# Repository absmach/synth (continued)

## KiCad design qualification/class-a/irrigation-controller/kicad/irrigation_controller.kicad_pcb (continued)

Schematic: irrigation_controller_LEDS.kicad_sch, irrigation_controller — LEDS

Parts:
D_N1: (no value); LED_0603_1608Metric
D_PWR: LTST-C190KGKT; LED_0603_1608Metric; MPN LTST-C190KGKT
D_VALVE: (no value); LED_0603_1608Metric
R_LV: 680; R_0603_1608Metric
R_N3: 2.2k; R_0603_1608Metric
R_PWR: 680; R_0603_1608Metric

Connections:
+3V3: R_PWR.1; also elsewhere on the board
+12V_VALVE: R_N3.1; also elsewhere on the board
GND: D_N1.1 (K), D_PWR.1 (K), D_VALVE.1 (K); also elsewhere on the board
LED_N12_A: D_N1.2 (A), R_N3.2
LED_PWR_A: D_PWR.2 (A), R_PWR.2
LED_VALVE_A: D_VALVE.2 (A), R_LV.2
LED_VALVE_DRV: R_LV.1; also elsewhere on the board

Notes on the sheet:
LEDS
D_PWR lit when +3V3 is present. D_VALVE lit when firmware commands either valve on.
D_N1 lit when +12V_VALVE is present (R_N3).
LED currents are I = (V - Vf) / R, with Vf from the LED datasheets: Lite-On LTST-C190KGKT 1.9 to 2.4 V at 20 mA (green LED D_PWR), KENTO KT-0603Y 2.4 V (amber LEDs D_VALVE and D_N1, from its LCSC listing). D_PWR, R_PWR 680 on +3V3: 1.3 to 2.1 mA, at most 4.85 mA with Vf = 0. D_VALVE, R_LV 680, driv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

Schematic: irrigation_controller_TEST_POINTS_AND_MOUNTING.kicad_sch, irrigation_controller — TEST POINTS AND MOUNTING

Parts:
H1, H2, H3, H4: (no value); MountingHole_2.5mm
TP_N1, TP_N2: (no value); TestPoint_Pad_D1.5mm

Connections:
+3V3: TP_N1.1; also elsewhere on the board
GND: TP_N2.1; also elsewhere on the board

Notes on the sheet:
TEST POINTS AND MOUNTING
TP_N1 on +3V3, TP_N2 on GND.
Four M2.5 mounting holes at the corners.

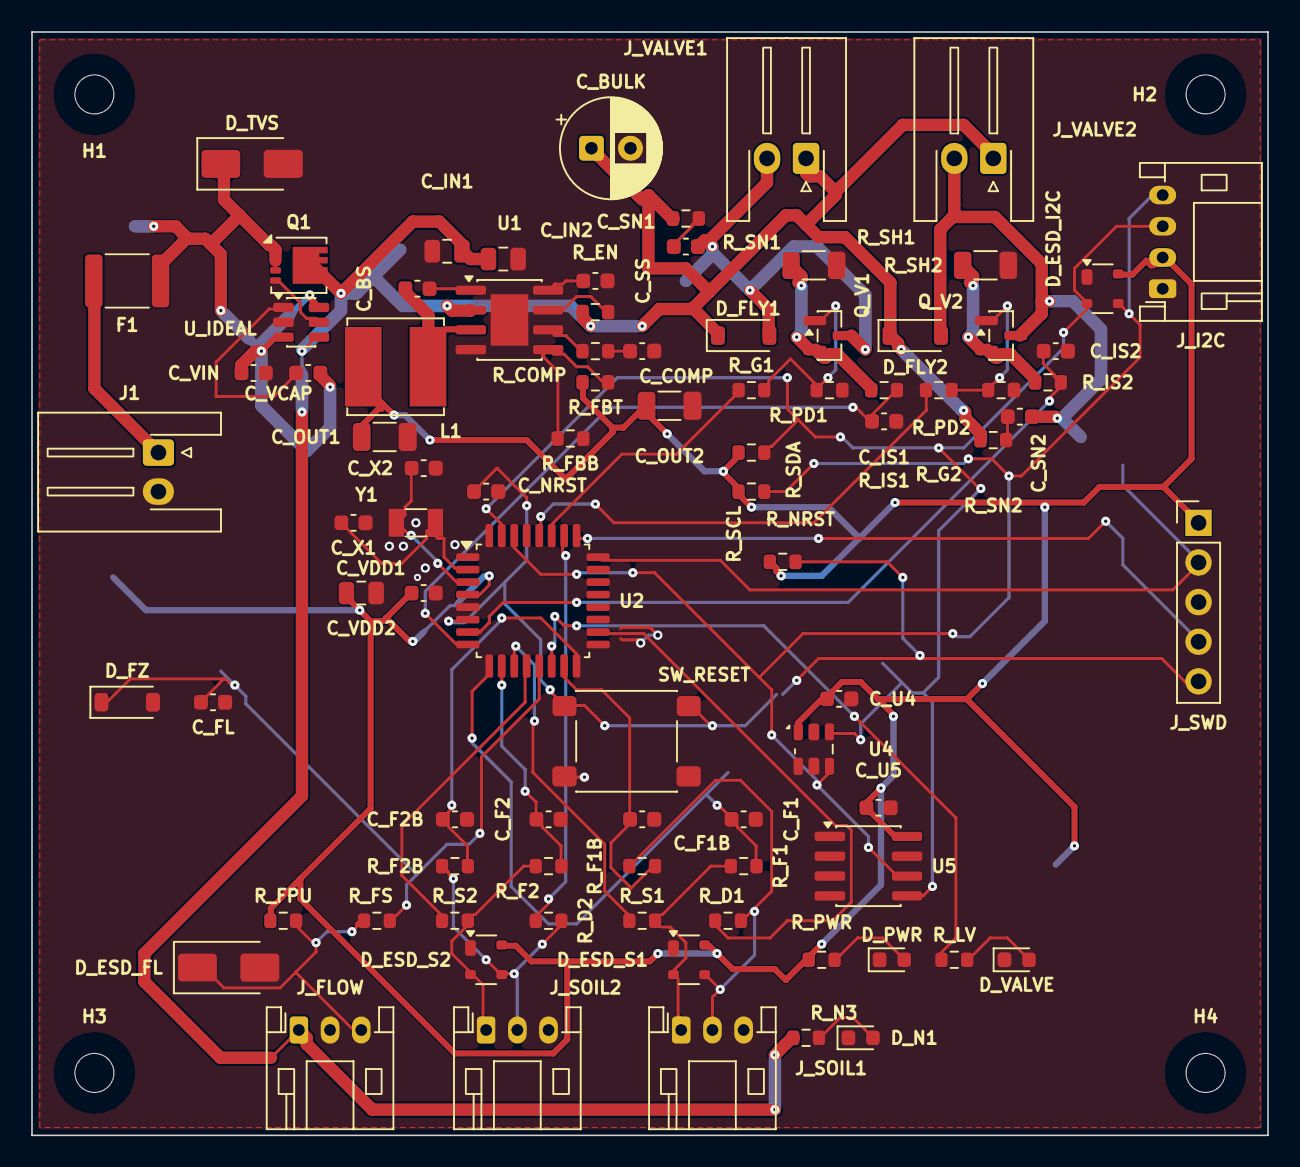
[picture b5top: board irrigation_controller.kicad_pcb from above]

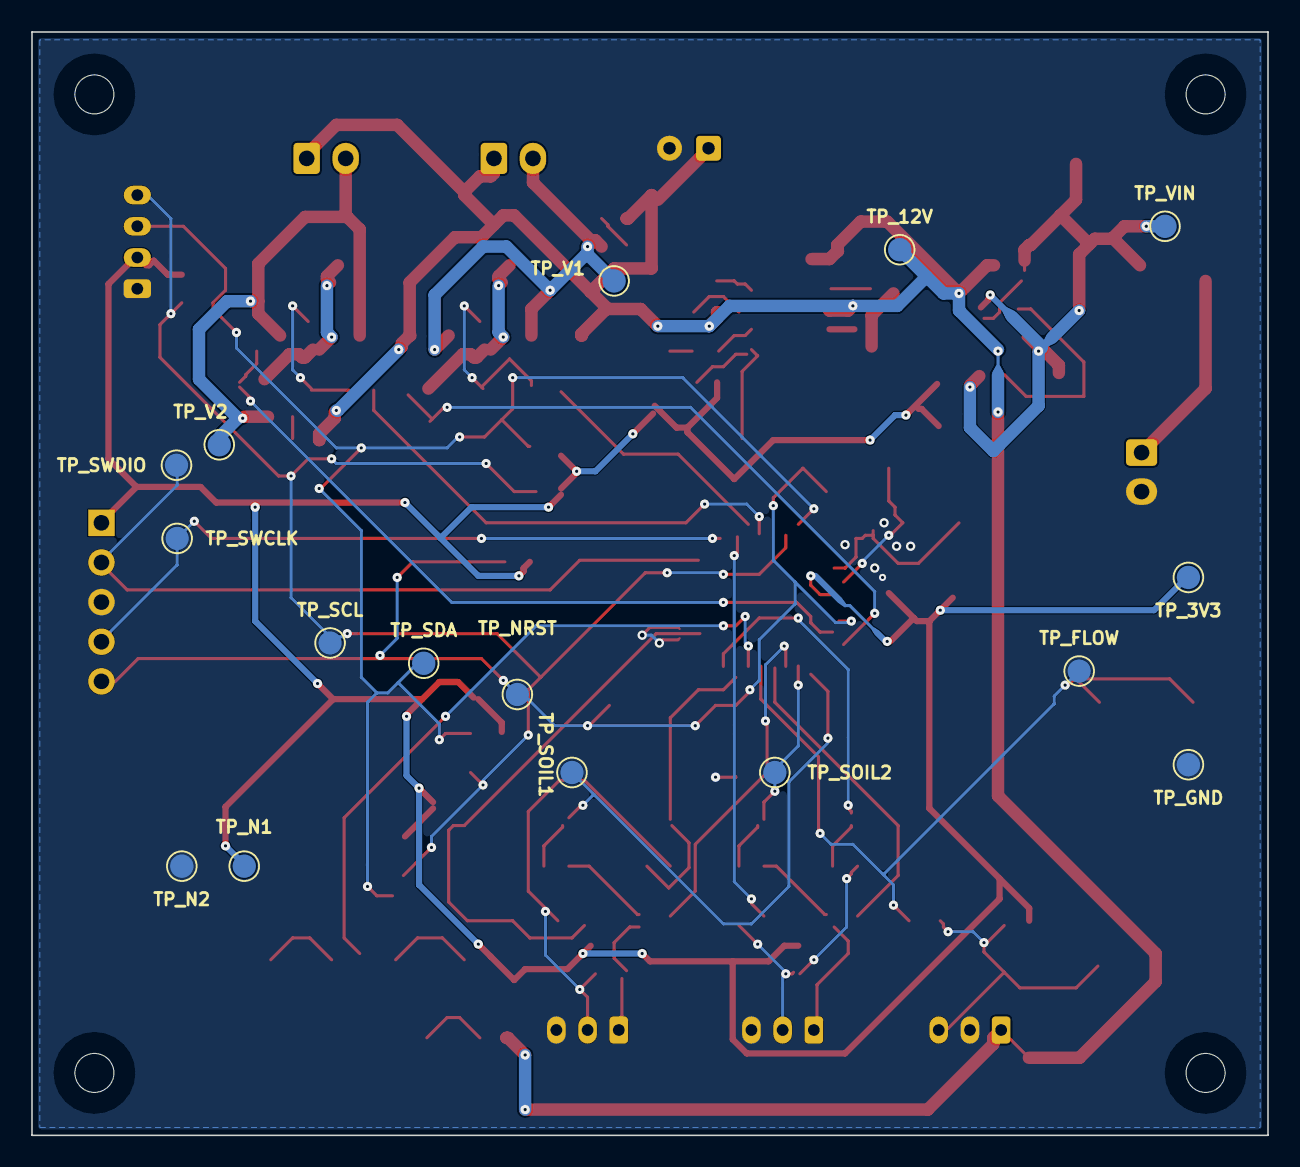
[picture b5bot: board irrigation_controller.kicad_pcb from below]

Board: 2 copper layers, 79.2 x 70.7 mm, 107 parts (16 on the bottom side), 51 nets.

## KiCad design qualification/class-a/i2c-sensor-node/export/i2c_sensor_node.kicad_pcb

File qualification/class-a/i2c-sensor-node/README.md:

# I2C sensor node with a 5 V JST input (Class A, case 2)

A field sensor node: an STM32G030F6P6 microcontroller reads a Bosch BME680 (temperature, humidity, pressure and gas) and a 24LC256 EEPROM over one I2C bus. It runs from 5 V on a JST XH connector, with an AMS1117-3.3 making the 3.3 V rail. The board has two copper layers with a GND pour on each and measures 84.0 x 50.0 mm.

Case 2 is claimed for a plain default export of a protected, low-speed board: every external line has a series resistor and a 3.3 V clamp, and every net is a static or slow line. No firmware has run on the board and no board has been built.

The prompt to reproduce the board is in [`PROMPT.md`](PROMPT.md), written from the finished board. The prompts the agent ran are in the history at `dcf1e328`.

## The board

### Parts

| Group            | Parts                                                                                                                                                                                                         |
| ---------------- | ------------------------------------------------------------------------------------------------------------------------------------------------------------------------------------------------------------- |
| 5 V input        | `J1` JST S2B-XH-A-1; `F1` Littelfuse 1812L050/60MR (0.5 A hold); `D1` 1N5819HW Schottky against reverse polarity; `D4` Nexperia PTVS6V0S1UR (6 V standoff, 10.3 V maximum clamp per the distributor listings) |
| 3.3 V            | `U1` AMS1117-3.3 (SOT-223); `C1`, `C2` 10 uF on the input; `C3` 47 uF tantalum, `C4` 10 uF and `C5` 100 nF on the output; power LED `D15` with `R24`                                                          |
| Microcontroller  | `U2` STM32G030F6P6 (TSSOP-20); `C6` 100 nF and `C7` 4.7 uF on VDD; `R3` 10 k, `C8` 100 nF and `SW1` on NRST; `J4` 1x5 SWD header behind `R13`, `R14` (100 ohm), with 3.3 V zeners `D8`, `D9`, `D19`           |
| I2C sensing      | `U3` BME680 and `U5` 24LC256 on one bus (PB7 SDA, PB6 SCL), pull-ups `R9`, `R10` (4.7 k), decoupling `C10` to `C12`                                                                                           |
| Serial connector | `J3` JST S4B-PH-K-S: UART TX through `R11` (330 ohm) and `D7`, RX through `R12` (1 k) and `D24`, 3.3 V sense and ground                                                                                       |
| GPIO header      | `J5` 1x12 header: eight MCU lines (ADC, SPI and timer pins), each behind 330 ohm (`R15` to `R22`) with a 3.3 V zener (`D10` to `D13`, `D20` to `D23`); a 3.3 V sense line through `D14` and `R23` (100 ohm)   |
| Mounting         | `H2`, `H3`: two M2.5 non-plated holes at opposite corners                                                                                                                                                     |

### Layout

| Item                    | Value                                                                                                                                                                                               |
| ----------------------- | --------------------------------------------------------------------------------------------------------------------------------------------------------------------------------------------------- |
| Outline                 | 84.0 x 50.0 mm                                                                                                                                                                                      |
| Copper layers           | 2 (F.Cu, B.Cu)                                                                                                                                                                                      |
| Stackup                 | 1.6 mm board thickness                                                                                                                                                                              |
| Parts in the BOM        | 57 lines: 55 parts and 2 non-plated mounting holes (`H2`, `H3`)                                                                                                                                     |
| Parts placed in the CPL | 55, all on the top side                                                                                                                                                                             |
| Nets                    | 35 named nets, counted on the board file                                                                                                                                                            |
| Track segments          | 422                                                                                                                                                                                                 |
| Vias                    | 142                                                                                                                                                                                                 |
| Track length            | 1239.4 mm                                                                                                                                                                                           |
| Zones and planes        | GND pour on F.Cu and on B.Cu; keepout zones for the `H2` and `H3` screw heads (no tracks, vias or copper pour)                                                                                      |
| Net classes             | `PWR` 0.5 mm, `V33` 0.4 mm, `GNDC` 0.4 mm and `SIG` 0.25 mm, declared in the source; `PWR`, `V33` and `SIG` declare `edge_rate slow`                                                                |
| Fab package             | `fab/gerbers.zip` (copper, mask, paste, silkscreen, outline, drill and job file), `fab/bom.csv`, `fab/cpl.csv`; KiCad project in `kicad/`, STEP model in `models/`, images in `images/`             |
| Source                  | `i2c_sensor_node.synth` with the placement sidecar `i2c_sensor_node.placement.layout.toml`; made with `synth mcp` from a prompt and exported through the Synth MCP server (the `synth_export` tool) |

### Checks

| Check                              | Result                                       | Notes                                                                     |
| ---------------------------------- | -------------------------------------------- | ------------------------------------------------------------------------- |
| KiCad DRC (10.0.8, --refill-zones) | 0 errors, 57 warnings, 0 unconnected         | Warnings: 55 lib_footprint_mismatch, 2 track_dangling                     |
| KiCad ERC (10.0.8)                 | 0 errors, 6 warnings, 0 unconnected          | Warnings: 5 lib_symbol_issues, 1 pin_to_pin                               |
| Signal class                       | No clock, differential or switching-node net | Every net is a static or slow line, as declared in the source net classes |

### Design figures

| Area             | Item                              | Value                                                                                                                             | Basis                                                                                                  |
| ---------------- | --------------------------------- | --------------------------------------------------------------------------------------------------------------------------------- | ------------------------------------------------------------------------------------------------------ |
| Power            | 3.3 V rail load budget            | 100 mA from 5 V                                                                                                                   | Stated in the source                                                                                   |
| Thermal          | `U1` dissipation at 100 mA        | (5.0 - 3.3) x 0.1 A = 0.17 W, a 15.3 C rise                                                                                       | Calculated with thetaJA 90 C/W from the AMS1117 datasheet as cited in the source; datasheet not opened |
| Thermal          | `U1` at 300 mA                    | 0.51 W, 45.9 C rise; the part's ceiling, not a supported load                                                                     | Calculated with thetaJA 90 C/W                                                                         |
| Power            | `C3` output capacitor             | 47 uF tantalum, where 22 uF is required                                                                                           | Stated in the source                                                                                   |
| Power            | Power LED current                 | 1.3 to 2.1 mA through 680 ohm at VF 1.9 to 2.4 V                                                                                  | Calculated                                                                                             |
| Protection       | Input order                       | Fuse `F1` first, then reverse-polarity diode `D1`; `D4` clamps +5V_PROT behind `D1`, so a reversed supply never forward-biases it | Stated in the source                                                                                   |
| Protection       | 5 V fault on a 330 ohm line       | (5 - 3.3) / 330 = 5.2 mA, 17 mW into its zener                                                                                    | Calculated                                                                                             |
| Protection       | 5 V fault on the 1 k UART RX line | 1.7 mA, 5.6 mW into `D24`                                                                                                         | Calculated                                                                                             |
| Protection       | 5 V fault on a 100 ohm SWD line   | (5 - 3.3) / 100 = 17 mA, 56 mW into `D8`, `D9` or `D19`                                                                           | Calculated                                                                                             |
| Protection       | 3.3 V sense line                  | At most 3 mA                                                                                                                      | Stated in the source                                                                                   |
| Signal integrity | I2C addresses                     | `U3` SDO (pin 5) tied to ground selects 0x76; `U5` A2:A0 low selects 0x50; no collision                                           | Stated in the source                                                                                   |
| Signal integrity | I2C pull-ups                      | One 4.7 k pair for the whole bus                                                                                                  | Stated in the source                                                                                   |
| Signal integrity | Unused pins                       | PA9 and PA10 (pins 16, 17) are unconnected                                                                                        | Stated in the source                                                                                   |
| Signal integrity | BOOT0                             | Shares PA14 and SWCLK; the default option bytes ignore it                                                                         | Stated in the source                                                                                   |
| Assembly         | SWD header `J4`                   | Pin 1 3.3 V sense, 2 SWDIO, 3 SWCLK, 4 GND, 5 NRST; use a J-Link or ST-LINK at 3.3 V logic                                        | Stated in the source                                                                                   |
| Assembly         | Reset                             | `SW1` and NRST on `J4` reset the chip                                                                                             | Stated in the source                                                                                   |
| Assembly         | UART connector `J3`               | Pin 1 GND, 2 UART_TX, 3 UART_RX, 4 3.3 V sense; host logic 3.3 V to 5 V                                                           | Stated in the source                                                                                   |
| Assembly         | GPIO header `J5`                  | Pin 1 3.3 V sense, 2 GND, 3 PA0, 4 PA1, 5 PA4, 6 GND, 7 PA5, 8 PA6, 9 PA7, 10 GND, 11 PB0, 12 PB9                                 | Stated in the source                                                                                   |

### Sourcing

| Item       | Status                                  | Notes                                          |
| ---------- | --------------------------------------- | ---------------------------------------------- |
| `U2`       | STM32G030F6P6TR, LCSC `C529330`         | Tape-and-reel code of the same TSSOP-20 part   |
| `SW1`      | C&K PTS645SM43SMTR92LFS, LCSC `C221880` | JLCPCB listing; re-check stock before ordering |
| `J5`       | XFCN PZ254V-11-12P, LCSC `C2840012`     | JLCPCB listing                                 |
| `J4`       | Hand-fitted, Farnell 1022253            | Harwin M20-9990546; also RS 681-2985           |
| `D4`       | Farnell (CPC) SC21458                   | No LCSC listing found                          |
| `H2`, `H3` | Board feature, no part                  | Non-plated holes                               |

## Not verified by Synth

| Area                  | What is not verified                                                                                                                            |
| --------------------- | ----------------------------------------------------------------------------------------------------------------------------------------------- |
| Routing reports       | The routing report and the return-via advisory list are not in this folder.                                                                     |
| Fabrication           | The JLCPCB DFM report and quote for this package are not in this folder.                                                                        |
| Reproducibility       | The three-export comparison and the Gerber content hash are not in this folder.                                                                 |
| Narrow copper         | The router draws 0.127 mm stubs at the pads of `U2`, below the class widths. The current they carry is not checked.                             |
| Part data             | Several BOM lines cite distributor listings only (for example `F1`, `D4`, `J5` and the `U1` thermal figures). Those datasheets were not opened. |
| Firmware and bring-up | No firmware has run and no board has been built.                                                                                                |
| Independent sign-off  | The independent PCB review required by #39 is still open.                                                                                       |

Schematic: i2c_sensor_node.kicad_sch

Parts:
C1, C2, C4: 10uF; C_0805_2012Metric
C3: 47uF; CP_EIA-3528-21_Kemet-B
C5, C6, C8, C10, C11, C12: 100nF; C_0603_1608Metric
C7: 4.7uF; C_0603_1608Metric
D1, D14: 1N5819; D_SOD-123; MPN 1N5819HW-7-F; LCSC C82544
D4: PTVS6V0S1UR; Nexperia_CFP3_SOD-123W; MPN PTVS6V0S1UR
D7, D8, D9, D10, D11, D12, D13, D19, D20, D21, D22, D23, D24: 3.3V zener; D_SOD-123
D15: GREEN; LED_0603_1608Metric; MPN LTST-C190KGKT
F1: 0.5A hold; Fuse_1812_4532Metric
H2, H3: (no value); MountingHole_2.5mm
J1: JST S2B-XH-A-1; JST_XH_S2B-XH-A-1_1x02_P2.50mm_Horizontal
J3: JST S4B-PH-K-S; JST_PH_S4B-PH-K_1x04_P2.00mm_Horizontal
J4: SWD; PinHeader_1x05_P2.54mm_Vertical
J5: GPIO; PinHeader_1x12_P2.54mm_Vertical
R3: 10k; R_0603_1608Metric
R9, R10: 4.7k; R_0603_1608Metric
R11, R15, R16, R17, R18, R19, R20, R21, R22: 330; R_0603_1608Metric
R12: 1k; R_0603_1608Metric
R13, R14: 100; R_0603_1608Metric
R23: 100; R_0805_2012Metric
R24: 680; R_0603_1608Metric
SW1: RESET; SW_SPST_PTS645Sx43SMTR92
U1: AMS1117-3.3; SOT-223-3_TabPin2; MPN AMS1117-3.3; LCSC C6186
U2: STM32G030F6P6; TSSOP-20_4.4x6.5mm_P0.65mm; MPN STM32G030F6P6
U3: BME680; Bosch_LGA-8_3x3mm_P0.8mm_ClockwisePinNumbering; MPN BME680
U5: 24LC256-I/SN; SOIC-8_3.9x4.9mm_P1.27mm; MPN 24LC256-I/SN; LCSC C411625

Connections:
3V3_REF: J3.4, J4.1, J5.1, R23.2
+3V3: C3.1, C4.1, C5.1, C6.1, C7.1, C10.1, C11.1, C12.1, D14.2 (A), R3.1, R9.1, R10.1, R24.1, U1.2 (VO), U2.4 (VDD), U3.2 (CSB), U3.6 (VDDIO), U3.8 (VDD), U5.8 (VCC)
+5V_PROT: C1.1, C2.1, D1.1 (K), D4.1 (K), U1.3 (VI)
GND: C1.2, C2.2, C3.2, C4.2, C5.2, C6.2, C7.2, C8.2, C10.2, C11.2, C12.2, D4.2 (A), D7.2 (A), D8.2 (A), D9.2 (A), D10.2 (A), D11.2 (A), D12.2 (A), D13.2 (A), D15.1 (K), D19.2 (A), D20.2 (A), D21.2 (A), D22.2 (A), D23.2 (A), D24.2 (A), J1.2, J3.1, J4.4, J5.2, J5.6, J5.10, SW1.2, U1.1 (GND), U2.5 (VSS), U3.1 (GND), U3.5 (SDO), U3.7 (GND), U5.1 (A0), U5.2 (A1), U5.3 (A2), U5.4 (GND), U5.7 (WP)
GPIO_PA0: J5.3, R15.2
GPIO_PA0_MCU: D10.1 (K), R15.1, U2.7 (PA0)
GPIO_PA1: J5.4, R16.2
GPIO_PA1_MCU: D20.1 (K), R16.1, U2.8 (PA1)
GPIO_PA4: J5.5, R17.2
GPIO_PA4_MCU: D11.1 (K), R17.1, U2.11 (PA4)
GPIO_PA5: J5.7, R18.2
GPIO_PA5_MCU: D21.1 (K), R18.1, U2.12 (PA5)
GPIO_PA6: J5.8, R19.2
GPIO_PA6_MCU: D12.1 (K), R19.1, U2.13 (PA6)
GPIO_PA7: J5.9, R20.2
GPIO_PA7_MCU: D22.1 (K), R20.1, U2.14 (PA7)
GPIO_PB0: J5.11, R21.2
GPIO_PB0_MCU: D13.1 (K), R21.1, U2.15 (PA8/PB0/PB1/PB2)
GPIO_PB9: J5.12, R22.2
GPIO_PB9_MCU: D23.1 (K), R22.1, U2.2 (PB9/PC14)
I2C_SCL: R10.2, U2.20 (PB3/PB4/PB5/PB6), U3.4 (SCK), U5.6 (SCL)
I2C_SDA: R9.2, U2.1 (PB7/PB8), U3.3 (SDI), U5.5 (SDA)
LED_PWR: D15.2 (A), R24.2
NRST: C8.1, D19.1 (K), J4.5, R3.2, SW1.1, U2.6 (NRST)
REF_D: D14.1 (K), R23.1
SWCLK: D9.1 (K), J4.3, R14.2
SWCLK_MCU: R14.1, U2.19 (PA14/PA15)
SWDIO: D8.1 (K), J4.2, R13.2
SWDIO_MCU: R13.1, U2.18 (PA13)
U2_RX: D24.1 (K), R12.1, U2.10 (PA3)
U2_TX: D7.1 (K), R11.1, U2.9 (PA2)
UART_RX: J3.3, R12.2
UART_TX: J3.2, R11.2
VIN_5V_FUSED: D1.2 (A), F1.2
VIN_5V_RAW: F1.1, J1.1

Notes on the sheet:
5V INPUT: FUSE THEN DIODE
3V3 REGULATOR
STM32G030 MCU
I2C SENSING
UART BREAKOUT
GPIO HEADER
MOUNTING
J1 pin 1 = +5 V, pin 2 = GND (JST XHP-2). Fuse first, then the
reverse-polarity diode D1.
D4 clamps transients on +5V_PROT, behind D1 so a reversed supply never
forward-biases it.
AMS1117 tab is VOUT. Load budget 100 mA: P = (5.0 - 3.3) x 0.1 A =
0.17 W, thetaJA 90 C/W gives a 15 C rise (125 C limit).
LED (VF 1.9 to 2.4 V): 1.3 to 2.1 mA through 680 R. C3 is 47 uF
tantalum (22 uF required).
J4: 1 = 3V3_REF, 2 = SWDIO, 3 = SWCLK, 4 = GND, 5 = NRST. PA14 is
SWCLK and BOOT0.
D8, D9, D19 are 3.3 V zeners; a 5 V fault through 100 R is (5 - 3.3) /
100 = 17 mA, 56 mW.
BME680 SDO low = 0x76, CSB high = I2C. 24LC256 A2:A0 low = 0x50. No
collision.
One pull-up pair, 4.7k each, for the whole bus.
J3: 1 GND, 2 UART_TX, 3 UART_RX, 4 3V3_REF (3 mA max). Host logic 3.3
V to 5 V.
D7, D24 are 3.3 V zeners behind 330 R and 1 k: a 5 V fault is 5.2 mA
(17 mW) and 1.7 mA (5.6 mW).
J5: 1 3V3_REF, 2 GND, 3 PA0, 4 PA1, 5 PA4, 6 GND, 7 PA5, 8 PA6, 9 PA7,
10 GND, 11 PB0, 12 PB9.
D10..D13, D20..D23: one 3.3 V zener per line behind 330 R; a 5 V fault
is 5.2 mA, 17 mW. 3V3_REF is +3V3 through D14 and 100 R, 3 mA max.
H2, H3: two M2.5 non-plated mounting holes at opposite (diagonal)
corners.

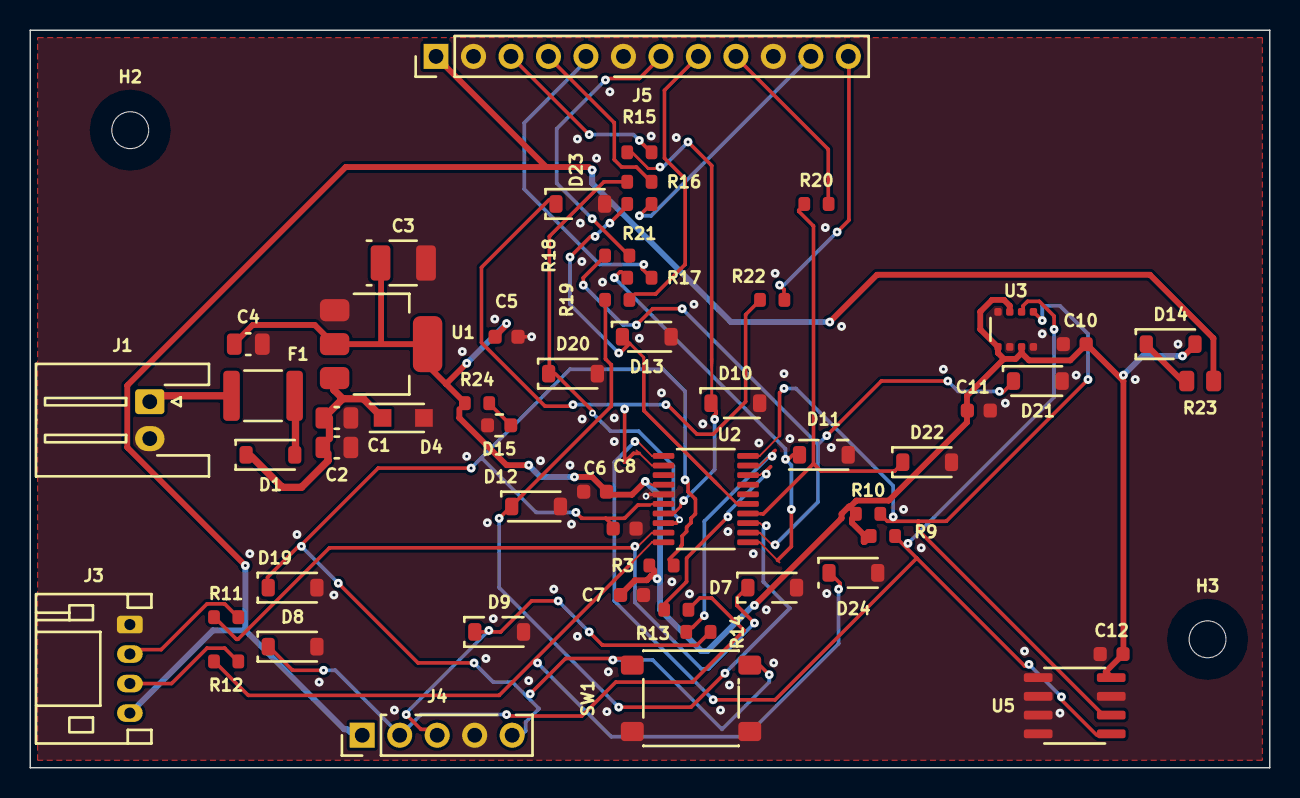
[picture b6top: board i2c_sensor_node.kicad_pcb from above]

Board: 2 copper layers, 84.0 x 50.0 mm, 57 parts (0 on the bottom side), 35 nets.

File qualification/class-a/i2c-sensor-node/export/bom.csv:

refdes,value,kind,description,kicad_symbol,kicad_footprint,lcsc_pn,mpn
C1,10uF,capacitor,"Generic 0805 MLCC, X7R/X5R, any value",Device:C,Capacitor_SMD:C_0805_2012Metric,,
C10,100nF,capacitor,"Generic 0603 MLCC, X7R/X5R, any value",Device:C,Capacitor_SMD:C_0603_1608Metric,,
C11,100nF,capacitor,"Generic 0603 MLCC, X7R/X5R, any value",Device:C,Capacitor_SMD:C_0603_1608Metric,,
C12,100nF,capacitor,"Generic 0603 MLCC, X7R/X5R, any value",Device:C,Capacitor_SMD:C_0603_1608Metric,,
C2,10uF,capacitor,"Generic 0805 MLCC, X7R/X5R, any value",Device:C,Capacitor_SMD:C_0805_2012Metric,,
C3,47uF,capacitor,"47µF 16V tantalum capacitor, polarised, 3528 case",Device:C_Polarized,Capacitor_Tantalum_SMD:CP_EIA-3528-21_Kemet-B,,
C4,10uF,capacitor,"Generic 0805 MLCC, X7R/X5R, any value",Device:C,Capacitor_SMD:C_0805_2012Metric,,
C5,100nF,capacitor,"Generic 0603 MLCC, X7R/X5R, any value",Device:C,Capacitor_SMD:C_0603_1608Metric,,
C6,100nF,capacitor,"Generic 0603 MLCC, X7R/X5R, any value",Device:C,Capacitor_SMD:C_0603_1608Metric,,
C7,4.7uF,capacitor,"Generic 0603 MLCC, X7R/X5R, any value",Device:C,Capacitor_SMD:C_0603_1608Metric,,
C8,100nF,capacitor,"Generic 0603 MLCC, X7R/X5R, any value",Device:C,Capacitor_SMD:C_0603_1608Metric,,
D1,1N5819,diode,"Diodes Inc. 1N5819HW-7-F, 40 V 1 A Schottky diode, SOD-123, low forward voltage",Device:D_Schottky,Diode_SMD:D_SOD-123,C82544,1N5819HW-7-F
D10,3.3V zener,diode,"3.3V Zener diode, SOD-123",Device:D_Zener,Diode_SMD:D_SOD-123,,
D11,3.3V zener,diode,"3.3V Zener diode, SOD-123",Device:D_Zener,Diode_SMD:D_SOD-123,,
D12,3.3V zener,diode,"3.3V Zener diode, SOD-123",Device:D_Zener,Diode_SMD:D_SOD-123,,
D13,3.3V zener,diode,"3.3V Zener diode, SOD-123",Device:D_Zener,Diode_SMD:D_SOD-123,,
D14,1N5819,diode,"Diodes Inc. 1N5819HW-7-F, 40 V 1 A Schottky diode, SOD-123, low forward voltage",Device:D_Schottky,Diode_SMD:D_SOD-123,C82544,1N5819HW-7-F
D15,GREEN,diode,"Lite-On LTST-C190KGKT green AlInGaP LED, 0603, Vf 1.9 to 2.4V at 20mA",Device:LED,LED_SMD:LED_0603_1608Metric,,LTST-C190KGKT
D19,3.3V zener,diode,"3.3V Zener diode, SOD-123",Device:D_Zener,Diode_SMD:D_SOD-123,,
D20,3.3V zener,diode,"3.3V Zener diode, SOD-123",Device:D_Zener,Diode_SMD:D_SOD-123,,
D21,3.3V zener,diode,"3.3V Zener diode, SOD-123",Device:D_Zener,Diode_SMD:D_SOD-123,,
D22,3.3V zener,diode,"3.3V Zener diode, SOD-123",Device:D_Zener,Diode_SMD:D_SOD-123,,
D23,3.3V zener,diode,"3.3V Zener diode, SOD-123",Device:D_Zener,Diode_SMD:D_SOD-123,,
D24,3.3V zener,diode,"3.3V Zener diode, SOD-123",Device:D_Zener,Diode_SMD:D_SOD-123,,
D4,PTVS6V0S1UR,diode,"Nexperia PTVS6V0S1UR 400 W unidirectional TVS, 6.0 V standoff, SOD123W, for VBUS and CC",Device:D_Zener,Diode_SMD:Nexperia_CFP3_SOD-123W,,PTVS6V0S1UR
D7,3.3V zener,diode,"3.3V Zener diode, SOD-123",Device:D_Zener,Diode_SMD:D_SOD-123,,
D8,3.3V zener,diode,"3.3V Zener diode, SOD-123",Device:D_Zener,Diode_SMD:D_SOD-123,,
D9,3.3V zener,diode,"3.3V Zener diode, SOD-123",Device:D_Zener,Diode_SMD:D_SOD-123,,
F1,0.5A hold,fuse,"Resettable polyfuse (PPTC), 0.5 A hold, 2-pin, 1812. Generic: MPN needs sourcing.",Device:Polyfuse,Fuse:Fuse_1812_4532Metric,,
H2,(no value),mounting_hole,M2.5 non-plated mounting hole (NPTH) for a board corner,Mechanical:MountingHole,MountingHole:MountingHole_2.5mm,,
H3,(no value),mounting_hole,M2.5 non-plated mounting hole (NPTH) for a board corner,Mechanical:MountingHole,MountingHole:MountingHole_2.5mm,,
J1,JST S2B-XH-A-1,connector,"JST XH-series 2-pin wire-to-board connector, 2.0mm pitch",Connector_Generic:Conn_01x02,Connector_JST:JST_XH_S2B-XH-A-1_1x02_P2.50mm_Horizontal,,
J3,JST S4B-PH-K-S,connector,"JST PH-series 4-pin wire-to-board connector, 2.0mm pitch",Connector_Generic:Conn_01x04,Connector_JST:JST_PH_S4B-PH-K_1x04_P2.00mm_Horizontal,,
J4,SWD,connector,"1x5 through-hole pin header, 2.54 mm pitch (SWD); datasheet_url is the product page of the Harwin M20 series, no manufacturer PDF link was verifiable",Connector_Generic:Conn_01x05,Connector_PinHeader_2.54mm:PinHeader_1x05_P2.54mm_Vertical,,
J5,GPIO,connector,"1x12 through-hole pin header, 2.54 mm pitch (GPIO); datasheet_url is the product page of the Harwin M20 series, no manufacturer PDF link was verifiable",Connector_Generic:Conn_01x12,Connector_PinHeader_2.54mm:PinHeader_1x12_P2.54mm_Vertical,,
R10,4.7k,resistor,"Generic 0603 thick-film resistor, any value",Device:R_US,Resistor_SMD:R_0603_1608Metric,,
R11,330,resistor,"Generic 0603 thick-film resistor, any value",Device:R_US,Resistor_SMD:R_0603_1608Metric,,
R12,1k,resistor,"Generic 0603 thick-film resistor, any value",Device:R_US,Resistor_SMD:R_0603_1608Metric,,
R13,100,resistor,"Generic 0603 thick-film resistor, any value",Device:R_US,Resistor_SMD:R_0603_1608Metric,,
R14,100,resistor,"Generic 0603 thick-film resistor, any value",Device:R_US,Resistor_SMD:R_0603_1608Metric,,
R15,330,resistor,"Generic 0603 thick-film resistor, any value",Device:R_US,Resistor_SMD:R_0603_1608Metric,,
R16,330,resistor,"Generic 0603 thick-film resistor, any value",Device:R_US,Resistor_SMD:R_0603_1608Metric,,
R17,330,resistor,"Generic 0603 thick-film resistor, any value",Device:R_US,Resistor_SMD:R_0603_1608Metric,,
R18,330,resistor,"Generic 0603 thick-film resistor, any value",Device:R_US,Resistor_SMD:R_0603_1608Metric,,
R19,330,resistor,"Generic 0603 thick-film resistor, any value",Device:R_US,Resistor_SMD:R_0603_1608Metric,,
R20,330,resistor,"Generic 0603 thick-film resistor, any value",Device:R_US,Resistor_SMD:R_0603_1608Metric,,
R21,330,resistor,"Generic 0603 thick-film resistor, any value",Device:R_US,Resistor_SMD:R_0603_1608Metric,,
R22,330,resistor,"Generic 0603 thick-film resistor, any value",Device:R_US,Resistor_SMD:R_0603_1608Metric,,
R23,100,resistor,"Generic 0805 thick-film resistor, any value",Device:R_US,Resistor_SMD:R_0805_2012Metric,,
R24,680,resistor,"Generic 0603 thick-film resistor, any value",Device:R_US,Resistor_SMD:R_0603_1608Metric,,
R3,10k,resistor,"Generic 0603 thick-film resistor, any value",Device:R_US,Resistor_SMD:R_0603_1608Metric,,
R9,4.7k,resistor,"Generic 0603 thick-film resistor, any value",Device:R_US,Resistor_SMD:R_0603_1608Metric,,
SW1,RESET,switch,Generic SPST tactile button,Switch:SW_Push,Button_Switch_SMD:SW_SPST_PTS645Sx43SMTR92,,
U1,AMS1117-3.3,regulator,"AMS1117-3.3 fixed 3.3V LDO regulator, SOT-223 — common JLC stock",Regulator_Linear:AMS1117-3.3,Package_TO_SOT_SMD:SOT-223-3_TabPin2,C6186,AMS1117-3.3
U2,STM32G030F6P6,mcu,"STMicro STM32G030F6P6 Cortex-M0+ 64 MHz, 32 KB flash, 8 KB RAM, TSSOP-20. Pin map checked against KiCad MCU_ST_STM32G0:STM32G030F6Px",MCU_ST_STM32G0:STM32G030F6Px,Package_SO:TSSOP-20_4.4x6.5mm_P0.65mm,,STM32G030F6P6
U3,BME680,sensor,"Bosch BME680 T/RH/P/gas sensor, 3.0x3.0 mm 8-pin LGA, I2C/SPI. Pins checked against KiCad Sensor:BME680; footprint is the 3x3 mm 0.8 mm pitch one whose KiCad description cites the BME680 datasheet",Sensor:BME680,Package_LGA:Bosch_LGA-8_3x3mm_P0.8mm_ClockwisePinNumbering,,BME680
U5,24LC256-I/SN,memory,"Microchip 24LC256-I/SN 256 Kbit I2C EEPROM, SOIC-8. Pin map checked against KiCad Memory_EEPROM:24LC256",Memory_EEPROM:24LC256,Package_SO:SOIC-8_3.9x4.9mm_P1.27mm,C411625,24LC256-I/SN

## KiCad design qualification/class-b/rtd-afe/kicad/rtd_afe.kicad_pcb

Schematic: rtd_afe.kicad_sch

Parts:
C_AV1: 330nF; C_0603_1608Metric; Voltage 10V; MPN 0603B334K500NT; LCSC C188679
C_AV2: 10uF; C_0805_2012Metric; Voltage 10V; MPN TCC0805X7R106K160FT; LCSC C380347
C_AVF: 4.7uF; C_0603_1608Metric; Voltage 10V; MPN TCC0603X7R475K100CT; LCSC C18185770
C_CM1, C_CM2: 10nF; C_0603_1608Metric; Voltage 50V; MPN 0603N103J500CT; LCSC C2894187
C_D: 100nF; C_0603_1608Metric; Voltage 50V
C_DV, C_DV1, C_DV2: 100nF; C_0603_1608Metric; Voltage 10V; MPN CC0603KRX7R9BB104; LCSC C14663
C_DVB: 4.7uF; C_0805_2012Metric; Voltage 10V; MPN CC0805KKX7R8BB475; LCSC C354262
C_F: 10nF; C_0603_1608Metric; Voltage 50V; MPN 0603N103J500CT; LCSC C2894187
C_FL: 100nF; C_0603_1608Metric; Voltage 10V; MPN CC0603KRX7R9BB104; LCSC C14663
C_IO, C_IO1, C_IO2, C_IO3, C_IO4: 100nF; C_0603_1608Metric; Voltage 10V; MPN CC0603KRX7R9BB104; LCSC C14663
C_L1, C_L2: 2.2uF; C_0603_1608Metric; Voltage 16V; MPN 0603B225K160NT; LCSC C43922
C_RI: 1uF; C_0603_1608Metric; Voltage 10V; MPN 0603B105K160NT; LCSC C93816
C_RO: 1uF; C_0603_1608Metric; Voltage 10V; MPN 0603B105K160NT; LCSC C93816
C_RV: 1uF; C_0603_1608Metric; Voltage 10V; MPN 0603B105K160NT; LCSC C93816
C_VI: 4.7uF; C_0603_1608Metric; Voltage 10V; MPN TCC0603X7R475K100CT; LCSC C18185770
C_X1, C_X2: 33pF; C_0603_1608Metric; Voltage 50V; MPN CL10C330JB8NNNC; LCSC C1663
D1, D2: ESD; D_SOD-323; MPN ESD5V0B03-323; LCSC C521915
H1, H2, H3, H4: (no value); MountingHole_2.5mm
J1: TYPE-C-31-M-12; USB_C_Receptacle_HRO_TYPE-C-31-M-12; MPN TYPE-C-31-M-12; LCSC C165948
J2: PT100; PinHeader_1x04_P2.54mm_Vertical; MPN PZ254V-11-04P; LCSC C492403
J3: SWD; PinHeader_1x03_P2.54mm_Vertical; MPN PZ254V-11-03P; LCSC C2937625
L1: 3.3uH; L_0805_2012Metric
L2: 600R@100MHz; L_0603_1608Metric; MPN BLM18AG601SN1D; LCSC C19330
R_AV: 33; R_0603_1608Metric; MPN FRC0603F33R0TS; LCSC C2909394
R_BIAS: 1k; R_0603_1608Metric; Tolerance 0.1%; MPN RT0603BRD071KL; LCSC C110776
R_CC1, R_CC2: 5.1k; R_0603_1608Metric; MPN 0603WAF5101T5E; LCSC C23186
R_DN: 27; R_0603_1608Metric; MPN 0603WAF270JT5E; LCSC C25190
R_DP: 27; R_0603_1608Metric; MPN 0603WAF270JT5E; LCSC C25190
R_RST: 10k; R_0603_1608Metric; MPN 0603WAF1002T5E; LCSC C25804
R_RUN: 10k; R_0603_1608Metric; MPN 0603WAF1002T5E; LCSC C25804
R_S1, R_S2: 1k; R_0603_1608Metric; Tolerance 0.1%; MPN RT0603BRD071KL; LCSC C110776
R_X: 1k; R_0603_1608Metric; MPN 0603WAF1001T5E; LCSC C21190
U1: ADS124S08IRHBR; Texas_RHB0032M_VQFN-32-1EP_5x5mm_P0.5mm_EP2.1x2.1mm; MPN ADS124S08IRHBR
U2: RP2350A; QFN-60-1EP_7x7mm_P0.4mm_EP3.4x3.4mm; MPN RP2350A; LCSC C14663
U3: REF5025AIDR; SOIC-8_3.9x4.9mm_P1.27mm; MPN REF5025AIDR
U4: W25Q128JVSIQ; SOIC-8_3.9x4.9mm_P1.27mm; MPN W25Q128JVSIQ; LCSC C97521
U5: LDO; SOT-23-5; MPN LP5907MFX-3.3/NOPB; LCSC C80670
Y1: 12MHz; Crystal_SMD_3225-4Pin_3.2x2.5mm; MPN ECS-120-20-33-TR

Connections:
+3V3: C_DV.1, C_FL.1, C_IO.1, C_IO1.1, C_IO2.1, C_IO3.1, C_IO4.1, C_L2.1, C_VI.1, L2.1, R_AV.1, R_RST.1, R_RUN.1, U1.15 (iovdd), U1.16 (dvdd), U2.1 (IOVDD), U2.11 (IOVDD), U2.20 (IOVDD), U2.30 (IOVDD), U2.38 (IOVDD), U2.45 (IOVDD), U2.49 (VREG_VIN), U2.53 (USB_OTP_VDD), U2.54 (QSPI_IOVDD), U4.8 (VCC), U5.5 (OUT)
+3V3A: C_AV1.1, C_AV2.1, C_RI.1, L2.2, U1.26 (avdd), U3.2 (Vin)
+3V3_RP_A: C_AVF.1, R_AV.2, U2.44 (ADC_AVDD), U2.46 (VREG_AVDD)
ADC_DRDY: U1.13 (drdy_n), U2.7 (GPIO4)
ADC_RESET_N: R_RST.2, U1.18 (reset_n), U2.9 (GPIO6)
ADC_START: U1.8 (start_sync), U2.8 (GPIO5)
AIN1: C_CM1.1, C_D.1, R_S1.2, U1.6 (ain1)
AIN2: C_CM2.1, C_D.2, R_S2.2, U1.5 (ain2)
CC1: J1.A5 (CC1), R_CC1.1
CC2: J1.B5 (CC2), R_CC2.1
DVDD_1V1: C_DV1.1, C_DV2.1, C_DVB.1, L1.2, U2.6 (DVDD), U2.23 (DVDD), U2.39 (DVDD), U2.50 (VREG_FB)
GND: C_AV1.2, C_AV2.2, C_AVF.2, C_CM1.2, C_CM2.2, C_DV.2, C_DV1.2, C_DV2.2, C_DVB.2, C_F.2, C_FL.2, C_IO.2, C_IO1.2, C_IO2.2, C_IO3.2, C_IO4.2, C_L1.2, C_L2.2, C_RI.2, C_RO.2, C_RV.2, C_VI.2, C_X1.2, C_X2.2, D1.2 (A2), D2.2 (A2), J1.A1 (GND), J1.A12 (GND), J1.B1 (GND), J1.B12 (GND), J1.SH (SHIELD), J3.3, R_BIAS.2, R_CC1.2, R_CC2.2, U1.14 (dgnd), U1.17 (clk), U1.24 (refcom), U1.27 (avss), U1.28 (avss_sw), U1.29 (refn0), U1.33 (ep), U2.47 (VREG_PGND), U2.61 (GND), U3.4 (GND), U4.4 (GND), U5.2 (GND), Y1.2 (G), Y1.4 (G)
QSPI_SCLK: U2.56 (QSPI_SCLK), U4.6 (CLK)
QSPI_SD0: U2.57 (QSPI_SD0), U4.5 (DI/IO_{0})
QSPI_SD1: U2.59 (QSPI_SD1), U4.2 (DO/IO_{1})
QSPI_SD2: U2.58 (QSPI_SD2), U4.3 (~WP/IO_{2})
QSPI_SD3: U2.55 (QSPI_SD3), U4.7 (~HOLD/~RESET/IO_{3})
QSPI_SS: U2.60 (~QSPI_SS), U4.1 (~CS)
REFOUT: C_RO.1, U1.23 (refout)
RTD_FN: J2.4, R_BIAS.1
RTD_FP: C_F.1, J2.1, U1.7 (ain0)
RTD_SN: J2.3, R_S2.1
RTD_SP: J2.2, R_S1.1
RUN: R_RUN.2, U2.26 (RUN)
SPI_CS: U1.9 (cs_n), U2.3 (GPIO1)
SPI_MISO: U1.12 (dout_drdy), U2.2 (GPIO0)
SPI_MOSI: U1.10 (din), U2.5 (GPIO3)
SPI_SCK: U1.11 (sclk), U2.4 (GPIO2)
SWCLK: J3.1, U2.24 (SWCLK)
SWDIO: J3.2, U2.25 (SWDIO)
USB_DN: R_DN.2, U2.51 (USB_DM)
USB_DN_C: D2.1 (A1), J1.A7 (D-), J1.B7 (D-), R_DN.1
USB_DP: R_DP.2, U2.52 (USB_DP)
USB_DP_C: D1.1 (A1), J1.A6 (D+), J1.B6 (D+), R_DP.1
VBUS: C_L1.1, J1.A4 (VBUS), J1.A9 (VBUS), J1.B4 (VBUS), J1.B9 (VBUS), U5.1 (IN), U5.3 (EN)
VREF: C_RV.1, U1.30 (refp0), U3.6 (Vout)
VREG_LX: L1.1, U2.48 (VREG_LX)
XIN: C_X1.1, U2.21 (XIN), Y1.1
XOUT: R_X.1, U2.22 (XOUT)
XOUT_R: C_X2.1, R_X.2, Y1.3

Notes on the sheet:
MOUNTING
RTD INPUT
ADC
REFERENCE
ANALOG SUPPLY
MCU
USB-C READOUT
J2 pin 1 F+, pin 2 S+, pin 3 S-, pin 4 F-. PT100 4-wire; force pair carries the 1 mA IDAC current, sense pair reads the RTD.
R_S1/R_S2 1k with C_D 100nF across the pair and C_CM1/C_CM2 10nF to GND: differential corner 1/(2pi*2k*110nF) about 720 Hz, common-mode corner about 16 kHz.
C_D is 10x each C_CM so a capacitor mismatch turns into little differential error (TI input filter rule). C0G so the filter does not move the reading.
C_F 10nF decouples the force node F+ (IDAC output). R_BIAS 1k returns the IDAC current to GND and lifts the RTD common-mode to about 1.1 V.
AVDD from +3V3A (ferrite-filtered), DVDD and IOVDD from +3V3. AVSS, AVSS_SW, REFN0, REFCOM, the exposed pad and DGND (pin 14) are on GND: the ADC returns its own digital supply current to the same plane. CLK is tied to that ground to use the internal oscillator.
REFOUT has 1 uF to GND for the unused internal reference. RESET has a 10k pull-up to +3V3 and is also driven by the MCU.
AINCOM, AIN3..AIN11, REFP1/REFN1, GPIOs and pin 25 are left open.
REF5025 2.5 V, VIN from +3V3A, VOUT straight to REFP0 with 1 uF at the reference pin, GND to GND. TEMP, TRIM/NR, DNC and NC pins are open.
L2 filters +3V3 into the +3V3A analog rail for the ADC and the reference. Its DC resistance and the ADC/REF supply current are not computed here.
RP2350 runs from its on-chip regulator: VREG_VIN on +3V3, VREG_LX through L1 3.3uH to the 1.1 V DVDD net, VREG_FB on that net.
VREG_AVDD and ADC_AVDD are fed from +3V3 through R_AV 33R and C_AVF 4.7uF.
U4 W25Q128 on the QSPI pins is the boot flash. Y1 ECS-120-20-33-TR 12 MHz, CL 20 pF: 2x 33 pF load caps (33/2 + about 3 pF stray = 19.5 pF), R_X 1k on XOUT.
J3 SWD: pin 1 SWCLK, pin 2 SWDIO, pin 3 GND. RUN has a 10k pull-up to +3V3.
USB 2.0 device port, VBUS 5 V in. CC1/CC2 5.1k so a host sources 5 V. 27R series on D+/D-, ESD diodes at the connector.
VBUS feeds U5 LP5907-3.3 (250 mA) which makes the +3V3 digital rail. No VBUS fuse or TVS: see QUALIFICATION.md.
The RTD board is a bus-powered USB device: it draws a few tens of mA. No USB-C PD.

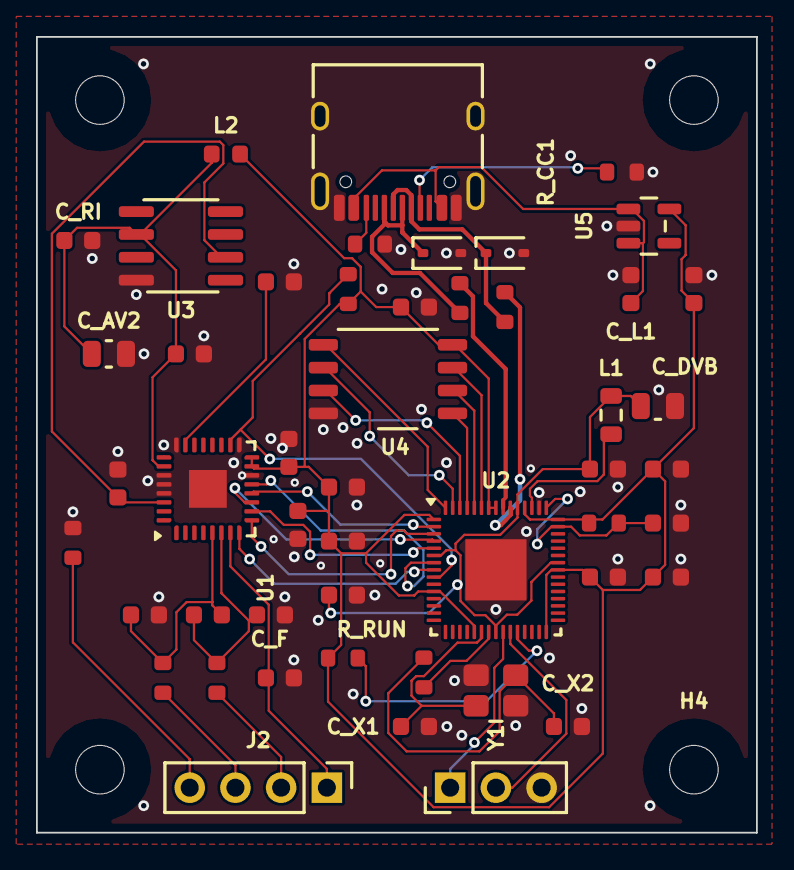
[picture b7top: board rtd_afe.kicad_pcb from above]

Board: 4 copper layers, 40.0 x 44.2 mm, 53 parts (0 on the bottom side), 40 nets.

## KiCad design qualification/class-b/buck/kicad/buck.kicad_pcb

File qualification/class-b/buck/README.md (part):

# 24 V to 3.3 V buck with protected input (Class B, SYN-67)

A 24 V in, 3.3 V out step-down board built around the TI LMR38010 (1 A), with a PTC fuse, a reverse-blocking Schottky and a TVS on the input. It is intended for 24 V +10% in and 1 A out, on four copper layers, 71.0 x 34.0 mm.

It answers ticket #67 under #38 (Class B qualification): a switching regulator with input and output filtering, feedback, power-good and thermal copper. The board is designed, placed and routed. It is not fabricated, not powered and not tested on hardware, and no surge rating is claimed.

The prompt to reproduce the board is in [`PROMPT.md`](PROMPT.md), written from the finished board. No agent prompt was kept; the nearest record is the cleaned brief in `absmach/synth-website` at `public/showcase/buck/prompt.md` (`22bc5390`).

## The board

### Parts

| Group               | Parts                                                                                                                                                                                                                                                                                                                           |
| ------------------- | ------------------------------------------------------------------------------------------------------------------------------------------------------------------------------------------------------------------------------------------------------------------------------------------------------------------------------- |
| Input               | `J1` JST B2B-XH-A; `F1` Bourns MF-MSMF110/33X PTC (1.1 A hold at 23 C, 0.63 A at 70 C, 2.2 A trip, 33 V max); `D1` Vishay SS36 Schottky, reverse block (60 V, 3 A); `D2` Vishay SMBJ30A TVS (30 V standoff, 48.4 V clamp at 12.4 A); `C1` 47 uF 50 V electrolytic (Honor RVT1H470M0810), `C2` 10 uF, `C3` 220 nF at the VIN pin |
| Converter           | `U1` TI LMR38010SDDAR, HSOIC-8 with exposed pad (4.2 to 80 V operating, 85 V absolute maximum); `C4` 100 nF boot; `R_RT` 33k sets 800 kHz; UVLO divider `R_UV_T` 1.37M and `R_UV_B` 100k                                                                                                                                        |
| Output              | `L1` Bourns SRN6045TA-6R8M, 6.8 uH (Isat 5.7 A); `C5`, `C6`, `C9` 22 uF 25 V X7R 1206; `J2` JST B4B-XH-A                                                                                                                                                                                                                        |
| Feedback            | `R_FB_T` 100k from the output node (L1 pad 2 side), `R_FB_B` 43.2k, `C7` 56 pF feed-forward across `R_FB_T`                                                                                                                                                                                                                     |
| Power-good and LEDs | `R_PG` 100k pull-up to +3V3, PG on `J2` pin 3; `D4` green "PG FAULT" with `R_PGLED` 470 ohm, lit while PG is low; `D3` green "PWR" with `R_LED` 470 ohm (both Lite-On LTST-C190KGKT)                                                                                                                                            |
| Mechanical          | `H1`, `H2` M2.5 non-plated holes in opposite corners                                                                                                                                                                                                                                                                            |
| Negative variant    | `buck_neg_fb_sw.synth` is the same board with `R_FB_T` and `C7` taken from SW instead of the output node. `synth validate` must reject it with E-SYNTH-POWER-011.                                                                                                                                                               |

### Layout

| Item                    | Value                                                                                                                                                                                      |
| ----------------------- | ------------------------------------------------------------------------------------------------------------------------------------------------------------------------------------------ |
| Outline                 | 71.0 x 34.0 mm                                                                                                                                                                             |
| Copper layers           | 4                                                                                                                                                                                          |
| Stackup                 | Default Synth four-layer stackup, 1.6 mm board                                                                                                                                             |
| Parts in the BOM        | 27                                                                                                                                                                                         |
| Parts placed in the CPL | 27                                                                                                                                                                                         |
| Nets                    | 13 named nets in `kicad/buck.kicad_pcb`                                                                                                                                                    |
| Track segments          | 97, all on F.Cu                                                                                                                                                                            |
| Vias                    | 21, all GND, 0.3 mm drill                                                                                                                                                                  |
| Track length            | 200.1 mm                                                                                                                                                                                   |
| Zones and planes        | One unsplit GND zone on each of the four copper layers; no analog or power ground split. Keepout zones at the `H1` and `H2` screw heads. No keepout under the switch node or the inductor. |
| Placement               | `buck.placement.layout.toml` pins all 27 parts with hard priority.                                                                                                                         |
| Fab package             | `fab/gerbers.zip`, `fab/bom.csv`, `fab/cpl.csv`, `models/buck.step` and `SHA256SUMS`                                                                                                       |
| Export pin              | The committed KiCad files were exported with Synth commit `a79570cd`. An export from another Synth revision does not match `SHA256SUMS`.                                                   |

### Checks

| Check                                            | Result                                                         | Notes                                                                                                                                                                                                      |
| ------------------------------------------------ | -------------------------------------------------------------- | ---------------------------------------------------------------------------------------------------------------------------------------------------------------------------------------------------------- |
| KiCad DRC (10.0.8, --refill-zones)               | 0 errors, 0 warnings, 0 unconnected                            | Measured on the committed `kicad/buck.kicad_pcb`.                                                                                                                                                          |
| KiCad ERC (10.0.8)                               | 0 errors, 8 warnings                                           | All 8 warnings are `lib_symbol_issues` (library lookups; the stock libraries were not configured in that run).                                                                                             |
| Schematic parity (KiCad 10.0.8)                  | Clean                                                          | Run on the committed files on 2026-11-25.                                                                                                                                                                  |
| Return vias (`W-SYNTH-DRC-016`)                  | 0                                                              | On the committed copper, with a 0.6377 mm window from the default four-layer stackup. Every layer change is a GND via and no signal net leaves F.Cu. This is a proximity test, not a return-path analysis. |
| `synth registry qualify`                         | All nine registry parts passed on 2026-10-29                   | `lmr38010`, `l_bourns_srn6045ta_6r8m`, `ss36`, `smbj30a`, `mf_msmf110_33x`, `jst_b2b_xh_a_2pin`, `jst_b4b_xh_a_4pin`, `c_electrolytic_smd_8x10`, `ltst_c190kgkt`.                                          |
| Registry QUAL warning                            | `mf_msmf110_33x` reports `E-SYNTH-QUAL-016`                    | Its 3D model is not installed.                                                                                                                                                                             |
| Schematic quality (`tools/schematic_quality.py`) | 7 texts with a wire through them, 1 wire crossing              | The sheet is readable, not tidy.                                                                                                                                                                           |
| Qualification matrix                             | Row `buck` in [`qualification/matrix.toml`](../../matrix.toml) | The row is skipped until the route and release verdicts are re-established.                                                                                                                                |

### Design figures

| Area       | Item                               | Value                                                                                                                        | Basis                                                    |
| ---------- | ---------------------------------- | ---------------------------------------------------------------------------------------------------------------------------- | -------------------------------------------------------- |
| Power      | Output voltage                     | Vout = 1.0 x (1 + 100k/43.2k) = 3.315 V typical; 3.26 to 3.36 V over the 0.985 to 1.015 V reference (ideal resistors)        | Calculated; TI SNVSBM3B                                  |
| Power      | UVLO thresholds                    | Start 18.4 V typical, stop 16.2 V typical                                                                                    | TI SNVSBM3B, Eq 13 and 14                                |
| Power      | UVLO spread                        | Start 16.2 to 20.6 V, stop 14.0 to 17.9 V                                                                                    | Calculated; TI SNVSBM3B, Eq 13 and 14                    |
| Power      | EN voltage                         | 1.90 V at 28 V in                                                                                                            | Calculated                                               |
| Power      | Inductor ripple                    | 0.53 A peak to peak at 26.4 V in                                                                                             | Calculated                                               |
| Power      | Inductor peak                      | About 1.27 A at 1 A out, against the 5.7 A Isat                                                                              | Calculated; Bourns SRN6045TA                             |
| Power      | Minimum inductance                 | 1.03 uH (Eq 11); 6.8 uH fitted                                                                                               | TI SNVSBM3B, Eq 11                                       |
| Power      | Input capacitance                  | Meets the 4.7 uF plus 100 to 220 nF minimum                                                                                  | TI SNVSBM3B                                              |
| Power      | Switching frequency                | `R_RT` 33k sets 800 kHz                                                                                                      | TI SNVSBM3B, RT table under Figure 8-4                   |
| Power      | Converter choice                   | The first revision used the LMR33640 (38 V absolute maximum), below the 48.4 V TVS clamp. The LMR38010 (85 V) sits above it. | TI SNVSBM3B; Vishay SMBJ series                          |
| Protection | TVS breakdown and clamp            | SMBJ30A breaks down at 33.3 to 36.8 V and clamps at 48.4 V; 600 W at 10/1000 us                                              | Vishay SMBJ series datasheet                             |
| Protection | Surge margin to converter          | 48.4 V clamp is below the LMR38010 85 V VIN and SW maximum                                                                   | TI SNVSBM3B; Vishay SMBJ series                          |
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
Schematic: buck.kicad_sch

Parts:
C1: 47uF; CP_Elec_8x10; Voltage 50V; MPN RVT1H470M0810
C2, C10, C11: 10uF; C_1206_3216Metric; Voltage 50V; MPN CL31B106KBHNNNE; LCSC C89632
C3: 220nF; C_0603_1608Metric; Voltage 50V
C4: 100nF; C_0603_1608Metric; Voltage 16V
C5, C6, C9: 22uF; C_1206_3216Metric; Voltage 25V; MPN CL31A226KAHNNNE; LCSC C12891
C7: 56pF; C_0603_1608Metric; Voltage 50V
D1: SS36; D_SMC; MPN SS36
D2: SMBJ30A; D_SMB; MPN SMBJ30A
D3: PWR; LED_0603_1608Metric; MPN LTST-C190KGKT
D4: PG FAULT; LED_0603_1608Metric; MPN LTST-C190KGKT
F1: 1.1A_PTC; Fuse_1812_4532Metric; MPN MF-MSMF110/33X
H1, H2: M2.5; MountingHole_2.5mm
J1: 24V_IN; JST_XH_B2B-XH-A_1x02_P2.50mm_Vertical; MPN B2B-XH-A
J2: 3V3_OUT; JST_XH_B4B-XH-A_1x04_P2.50mm_Vertical; MPN B4B-XH-A
L1: 6.8uH; L_Bourns_SRN6045TA; MPN SRN6045TA-6R8M
R_FB_B: 43.2k; R_0603_1608Metric; Tolerance 1%
R_FB_T: 100k; R_0603_1608Metric; Tolerance 1%
R_LED: 470; R_0603_1608Metric
R_PG: 100k; R_0603_1608Metric
R_PGLED: 470; R_0603_1608Metric
R_RT: 33k; R_0603_1608Metric; Tolerance 1%
R_UV_B: 100k; R_0603_1608Metric; Tolerance 1%
R_UV_T: 1.37M; R_0603_1608Metric; Tolerance 1%
U1: LMR38010SDDAR; HSOP-8-1EP_3.9x4.9mm_P1.27mm_EP2.41x3.1mm; MPN LMR38010SDDAR

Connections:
+3V3: C5.1, C6.1, C7.2, C9.1, J2.1, L1.2, R_FB_T.1, R_LED.1, R_PG.2, R_PGLED.1
BOOT: C4.1, U1.7 (boot)
EN: R_UV_B.1, R_UV_T.2, U1.2 (en)
FB: C7.1, R_FB_B.1, R_FB_T.2, U1.5 (fb)
GND: C1.2, C2.2, C3.2, C5.2, C6.2, C9.2, C10.2, C11.2, D2.2 (A), D3.1 (K), J1.2, J2.2, J2.4, R_FB_B.2, R_RT.2, R_UV_B.2, U1.1 (gnd), U1.9 (pad)
LED_PG: D4.2 (A), R_PGLED.2
LED_PWR: D3.2 (A), R_LED.2
PG: D4.1 (K), J2.3, R_PG.1, U1.6 (pg)
RT: R_RT.1, U1.4 (rt_sync)
SW: C4.2, L1.1, U1.8 (sw)
VIN: C1.1, C2.1, C3.1, C10.1, C11.1, D1.1 (K), D2.1 (K), R_UV_T.1, U1.3 (vin)
VIN_FUSED: D1.2 (A), F1.2
VIN_RAW: F1.1, J1.1

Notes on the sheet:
INPUT PROTECTION
INPUT FILTER
UVLO
BUCK
FEEDBACK
POWER GOOD
OUTPUT
MECHANICAL
J1 pin 1 is +24 V, pin 2 is GND.
F1 resettable PTC: Ihold 1.1 A, Vmax 33 V.
D1 Schottky in series blocks reverse polarity.
D2 TVS (30 V standoff) sits after D1, directly on the VIN node. Its 48.4 V clamp is below U1's 85 V absolute maximum, so U1 stays within its rating under a surge the TVS can absorb.
C1 bulk, C2, C10 and C11 ceramic, C3 high-frequency next to the VIN pin (LMR38010 section 9.2.2.6: at least 4.7 uF + 100 to 220 nF).
C2, C10 and C11 are three 10 uF 50 V X7R in parallel, about 2 uF each at 24 V bias (Samsung library data-sheet plot, approximate), about 6 uF effective, against the datasheet minimum of 4.7 uF (LMR38010 section 9.2.2.6).
50 V parts for a 24 V rail.
EN divider from VIN. LMR38010 VEN-H 1.25 V typical (1.1 to 1.4), VEN-L 1.10 V typical: start 18.4 V (16.2 to 20.6 V), stop 16.2 V.
EN stays under 2 V at a 28 V input (EN absolute maximum is VIN + 0.3 V).
LMR38010SDDAR: internal compensation, exposed pad (pin 9) on GND, open-drain PG, PFM with spread spectrum.
R_RT 33k from RT/SYNC to GND sets 800 kHz (RT table under datasheet Figure 8-4); the pin must not float.
C4 100 nF boot capacitor between BOOT and SW.
L1 6.8 uH at 800 kHz gives about 0.5 A ripple at 26.4 V in (datasheet Eq 10 K about 0.5), above the 1.03 uH minimum of Eq 11 (0.25 x 3.3 V / 800 kHz); 3x 22 uF is unverified: Table 9-1 has no 3.3 V row.
The exposed pad (pin 9) is soldered to the F.Cu GND pour. There are no vias in the pad:
the board's fabrication floor is a 0.3 mm drill and the KiCad thermal-via footprint ships 0.2 mm.
Vout = 1.0 V x (1 + 100k / 43.2k) = 3.31 V.
Divider taps the output node on the far side of L1, not SW.
C7 56 pF feed-forward across the upper resistor (datasheet Eq 9 gives about 60 pF).
PG is open drain and pulled up to +3V3 through 100k (datasheet 8.3.5: pull up through a resistor; PG tolerates 20 V).
PG goes low during start-up and on a fault, so J2 pin 3 reads valid only after the 4 ms start-up delay.
D4 green fault LED from +3V3 through R_PGLED to PG: it is lit while PG is low, dark while power is good.
About 2.5 mA when lit (470 R, Vf about 2.1 V); U1's PG pull-down is about 92 ohm RDSON, so PG stays near 0.4 V.
J2 pin 1 is +3.3 V, pin 2 GND, pin 3 power-good (3.3 V logic, 100k pull-up), pin 4 GND.
D3 green power LED from the 3.3 V rail.
Two M2.5 non-plated holes, H1 in the top middle and H2 at the right edge below J2; the board is fixed down through them.
